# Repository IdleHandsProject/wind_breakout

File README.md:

# WIND Breakout

## wind makes the feather fly.

WIND is a breakout board for the Adafruit Feather Series to make it easier to fly wire and put together a project with little to no soldering. 

It contains a battery holder for a 18650(I hate loose batteries!), a few buttons, and 5 pin headers for each pin(plus a proto section). There is a power switch connected to the Enable pin(shuts off the regulator), and a voltage divider to the A0 analog 
for monitoring battery voltage.  

This makes it easy to mount in a housing, and wire up different sensors you want to test.

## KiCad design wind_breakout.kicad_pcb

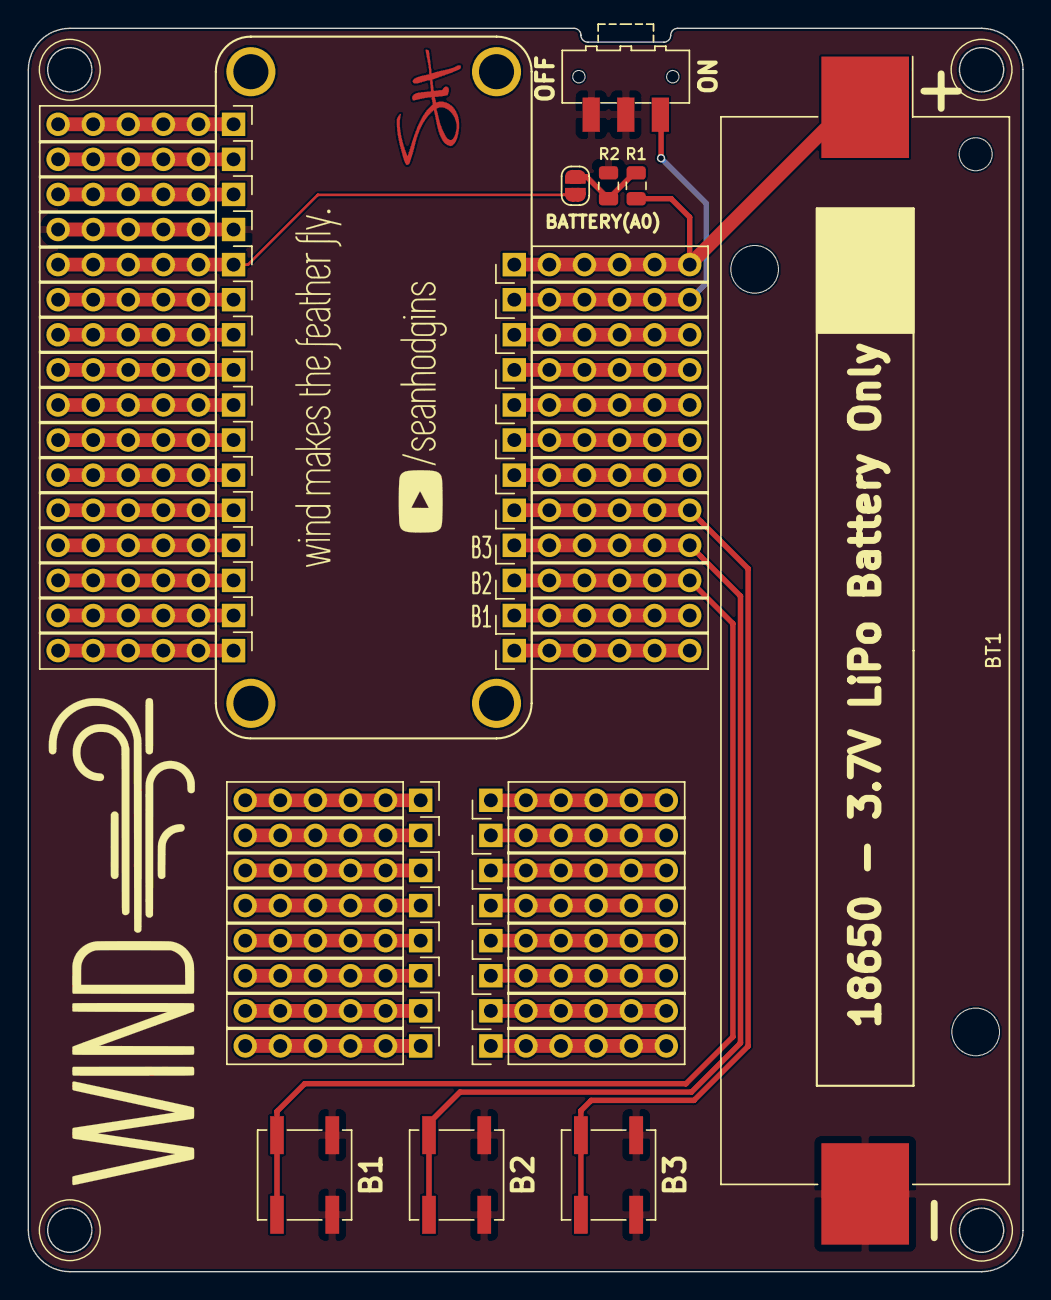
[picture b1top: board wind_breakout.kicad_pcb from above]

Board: 2 copper layers, 72.0 x 90.0 mm, 53 parts (0 on the bottom side), 45 nets.

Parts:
BT1: 18650; BatteryHolder_Keystone_1042_1x18650
J1: RESET; PinHeader_1x06_P2.54mm_Vertical
J2: A0; PinHeader_1x06_P2.54mm_Vertical
J3: A4; PinHeader_1x06_P2.54mm_Vertical
J4: MISO; PinHeader_1x06_P2.54mm_Vertical
J5: VBAT; PinHeader_1x06_P2.54mm_Vertical
J6: D12; PinHeader_1x06_P2.54mm_Vertical
J7: D6; PinHeader_1x06_P2.54mm_Vertical
J8: VCC; PinHeader_1x06_P2.54mm_Vertical
J9: A1; PinHeader_1x06_P2.54mm_Vertical
J10: A5; PinHeader_1x06_P2.54mm_Vertical
J11: D0; PinHeader_1x06_P2.54mm_Vertical
J12: EN; PinHeader_1x06_P2.54mm_Vertical
J13: D11; PinHeader_1x06_P2.54mm_Vertical
J14: D5; PinHeader_1x06_P2.54mm_Vertical
J15: AREF; PinHeader_1x06_P2.54mm_Vertical
J16: A2; PinHeader_1x06_P2.54mm_Vertical
J17: SCK; PinHeader_1x06_P2.54mm_Vertical
J18: D1; PinHeader_1x06_P2.54mm_Vertical
J19: VBUS; PinHeader_1x06_P2.54mm_Vertical
J20: D10; PinHeader_1x06_P2.54mm_Vertical
J21: SCL; PinHeader_1x06_P2.54mm_Vertical
J22: GND; PinHeader_1x06_P2.54mm_Vertical
J23: A3; PinHeader_1x06_P2.54mm_Vertical
J24: MOSI; PinHeader_1x06_P2.54mm_Vertical
J25: EXT; PinHeader_1x06_P2.54mm_Vertical
J26: D13; PinHeader_1x06_P2.54mm_Vertical
J27: D9; PinHeader_1x06_P2.54mm_Vertical
J28: SDA; PinHeader_1x06_P2.54mm_Vertical
J29, J30, J31, J32, J33, J34, J35, J36, J37, J38, J39, J40, J41, J42, J43, J44: Proto; PinHeader_1x06_P2.54mm_Vertical
JP1: batt_jmp; SolderJumper-2_P1.3mm_Open_RoundedPad1.0x1.5mm
PCB**: VAL**; PCB_FeatherWing_silk
R1: 100k; R_0805_2012Metric
R2: 200k; R_0805_2012Metric
SW1: SW_SPDT; SW_SPDT_CK-JS102011SAQN
SW2, SW3, SW4: SW_Push; SW_SPST_B3SL-1022P

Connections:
/A0: J2.1, J2.2, J2.3, J2.4, J2.5, J2.6, JP1.2
/A1: J9.1, J9.2, J9.3, J9.4, J9.5, J9.6
/A2: J16.1, J16.2, J16.3, J16.4, J16.5, J16.6
/A3: J23.1, J23.2, J23.3, J23.4, J23.5, J23.6
/A4: J3.1, J3.2, J3.3, J3.4, J3.5, J3.6
/A5: J10.1, J10.2, J10.3, J10.4, J10.5, J10.6
/AREF: J15.1, J15.2, J15.3, J15.4, J15.5, J15.6
/D0: J11.1, J11.2, J11.3, J11.4, J11.5, J11.6
/D1: J18.1, J18.2, J18.3, J18.4, J18.5, J18.6
/D5: J14.1, J14.2, J14.3, J14.4, J14.5, J14.6, SW2.1
/D6: J7.1, J7.2, J7.3, J7.4, J7.5, J7.6, SW3.1
/D9: J27.1, J27.2, J27.3, J27.4, J27.5, J27.6, SW4.1
/D10: J20.1, J20.2, J20.3, J20.4, J20.5, J20.6
/D11: J13.1, J13.2, J13.3, J13.4, J13.5, J13.6
/D12: J6.1, J6.2, J6.3, J6.4, J6.5, J6.6
/D13: J26.1, J26.2, J26.3, J26.4, J26.5, J26.6
/EN: J12.1, J12.2, J12.3, J12.4, J12.5, J12.6, SW1.1
/MISO: J4.1, J4.2, J4.3, J4.4, J4.5, J4.6
/MOSI: J24.1, J24.2, J24.3, J24.4, J24.5, J24.6
/SCK: J17.1, J17.2, J17.3, J17.4, J17.5, J17.6
/SCL: J21.1, J21.2, J21.3, J21.4, J21.5, J21.6
/SDA: J28.1, J28.2, J28.3, J28.4, J28.5, J28.6
/VBAT: BT1.1, J5.1, J5.2, J5.3, J5.4, J5.5, J5.6, R1.1
/VUSB: J19.1, J19.2, J19.3, J19.4, J19.5, J19.6
/~RESET: J1.1, J1.2, J1.3, J1.4, J1.5, J1.6
GND: BT1.2, J22.1, J22.2, J22.3, J22.4, J22.5, J22.6, R2.2, SW1.2, SW1.3, SW2.2, SW3.2, SW4.2
unnamed: J25.1, J25.2, J25.3, J25.4, J25.5, J25.6
unnamed: J29.1, J29.2, J29.3, J29.4, J29.5, J29.6
unnamed: J30.1, J30.2, J30.3, J30.4, J30.5, J30.6
unnamed: J31.1, J31.2, J31.3, J31.4, J31.5, J31.6
unnamed: J32.1, J32.2, J32.3, J32.4, J32.5, J32.6
unnamed: J33.1, J33.2, J33.3, J33.4, J33.5, J33.6
unnamed: J34.1, J34.2, J34.3, J34.4, J34.5, J34.6
unnamed: J35.1, J35.2, J35.3, J35.4, J35.5, J35.6
unnamed: J36.1, J36.2, J36.3, J36.4, J36.5, J36.6
unnamed: J37.1, J37.2, J37.3, J37.4, J37.5, J37.6
unnamed: J38.1, J38.2, J38.3, J38.4, J38.5, J38.6
unnamed: J39.1, J39.2, J39.3, J39.4, J39.5, J39.6
unnamed: J40.1, J40.2, J40.3, J40.4, J40.5, J40.6
unnamed: J41.1, J41.2, J41.3, J41.4, J41.5, J41.6
unnamed: J42.1, J42.2, J42.3, J42.4, J42.5, J42.6
unnamed: J43.1, J43.2, J43.3, J43.4, J43.5, J43.6
unnamed: J44.1, J44.2, J44.3, J44.4, J44.5, J44.6
unnamed: JP1.1, R1.2, R2.1
VCC: J8.1, J8.2, J8.3, J8.4, J8.5, J8.6

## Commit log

2019-05-13 readme updated
2019-06-10 video made at this point
2019-06-10 moved readme
2019-06-10 added video link
